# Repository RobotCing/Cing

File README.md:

| [**Úvod**](README.md) |[**Cing**](README-cing-sk.md)  |[**GalejeNextGen**](README-GNG-sk.md)|[**Kontakt**](README-kontakt.md)|[**English version**](README-en.md)|[**Arduino portable**](https://drive.google.com/file/d/1-qsKpOY3mSJC7BOQW4kqXe5UFbl79BuX/view?usp=sharing)|
|:---:|:---:|:---:|:---:|:---:|:---:|
|[Attiny 85](README-Attiny85.md)|[Attiny 84](README-Attiny84.md)|[Atmega 8](README-Atmega8.md)|[Attiny 13](README-Attiny13.md)|[Atmega 328](README-Atmega328.md)|[Atmega 32u4](README-Atmega32u4.md)|

## Úvod:

Každý pozná firmu [Lego](https://www.lego.com/en-us/). Vyrábajú najpopulárnejšie [Lego](https://www.lego.com/en-us/) stavebnice a sety. Vyrábajú <a href="https://www.lego.com/en-us/mindstorms">Lego NXT a Lego EV3</a> sety, ktoré sa jednoducho programujú a konštruujú, ale po naučení sa ich obrázkoveho jednoduchého programovacieho jazyka nemá užívaťeľ ďalšie možnosti ako programovať ich lego stavebnicu. Užívateľovi ostáva jediná možnosť - prejsť na inú platformu, napríklad [Arduino](https://www.arduino.cc/). 

[Arduino](https://www.arduino.cc/) je jedna z najlepších možností, nakoľko je lacnejšie ako akákoľvek iná platforma a taktiež je voľne dostupné. Ak sa užívateľ chce venovať [Arduinu](https://www.arduino.cc/), musí mať znalosti z elektroniky. Avšak tento fakt si mnoho ľudí uvedomí až keď si [Arduino](https://www.arduino.cc/) kúpi a vačšina z nich to vzdá. 

Preto sme vytvroli robota <a href="https://github.com/Galeje/Cing" target= "_blank">Cing</a> - je to multifunkčný a praktický robot pre všetky vekové kategórie od začiatočníkov až po expertov, nakoľko nie je potrebná žiadna znalosť z elektorniky či programovania. Pomocou nami vytvorených <a href="https://github.com/Galeje/Cing/tree/master/libraries" target= "_blank">knižníc</a>, ktoré umožňujü praktické a jednoduché využitie robota <a href="https://github.com/Galeje/Cing" target= "_blank">Cing</a> sa užívateľ naučí rýchlo, hravo a efektívne programovať.

Pre ešte ľahšie programovanie a učenie sa sme vytvorili príručky, ktoré obsahujú všetky programy a následne ich vysvetľujú. Aby užívateľ vedel, ako správne poskladať robota <a href="https://github.com/Galeje/Cing" target= "_blank">Cing</a>, použije opäť nami vytvorený manuál. Po naučení sa základných príkazov si môže vyskúšať cvičenia zo zbierky úloh na plátne s atrakciami.

Po zvládnutí základných aj pokročilých progamovacích príkazov môže používateľ použiť robota <a href="https://github.com/Galeje/Cing" target= "_blank">Cing</a> ako nástroj pre učenie sa elektroniky, nakoľko sa jednoducho dostane k schémam aj príručke, ako ho programovať bez použitia <a href="https://github.com/Galeje/Cing/tree/master/libraries" target= "_blank">knižníc</a>. To znamená, že užívateľ si môže vybrať, ako chce programovať <a href="https://github.com/Galeje/" target= "_blank">Cing-a</a>.

<!---Každú pozná firmu [Lego](https://www.lego.com/en-us/). Vyrábajú najpopulárnejšie [Lego](https://www.lego.com/en-us/) stavebnice a sety. Vyrábajú <a href="https://www.lego.com/en-us/mindstorms">Lego NXT and Lego EV3</a>sety ktoré sa jednoducho programujú a konštruujú, ale po naučení sa ich obrázkoveho jednoduchého programovacieho jazyka nemá užívaťeľ ďalšie možnosti ako programovat ich lego stavebnicu. Užívateľovi ostáva jediná možnosť - Prejisť na inú platformu napríklad [Arduino](https://www.arduino.cc/). [Arduino](https://www.arduino.cc/) je super možnosť nakoľko je Open Source, je lacnejšie, ale užívaťel musí rozumieť elektronike. Tento fakt si mnoho ľudí uvedomí až keď si [Arduino](https://www.arduino.cc/) kúpi a vačšina ľudí to vzdá.
<a href="https://github.com/Galeje/Cing" target= "_blank">Cing</a> rieši tento problém <a href="https://github.com/Galeje/Cing/tree/master/libraries" target= "_blank">knižnicami</a> ktoré umožňujú jednoduché programovanie <a href="https://github.com/Galeje/Cing" target= "_blank">Cing-a</a> v C programovaciom jazyku bez nutnosťi znalosti elektroniky. Taktiež sme vytvorili <a href="https://github.com/Galeje/Cing/blob/master/CINGtlac.pdf">príručky</a>, ktoré naučia užívateľa programovat <a href="https://github.com/Galeje/Cing" target= "_blank">Cing-a</a>.Po naučení sa základných aj pokročilých progamovacích príkazov môže používateľ použiť robota <a href="https://github.com/Galeje/Cing" target= "_blank">Cing</a> ako nástroj pre učenie sa elektroniky, nakoľko sa jednoducho dostane k schémam aj príručke ako ho programovať bez použitia <a href="https://github.com/Galeje/Cing/tree/master/libraries" target= "_blank">knižníc</a>. To znamená, že užívateľ si môže vybrať ako chce programovať <a href="https://github.com/Galeje/Cing" target= "_blank">Cing-a</a>.--->

Projekt používa <a href="https://github.com/MCUdude/MicroCore">MicroCore</a> a <a href="https://github.com/damellis">Damellis</a> <a href="https://github.com/damellis/attiny">ATtiny core</a>.

## Podporte nás:

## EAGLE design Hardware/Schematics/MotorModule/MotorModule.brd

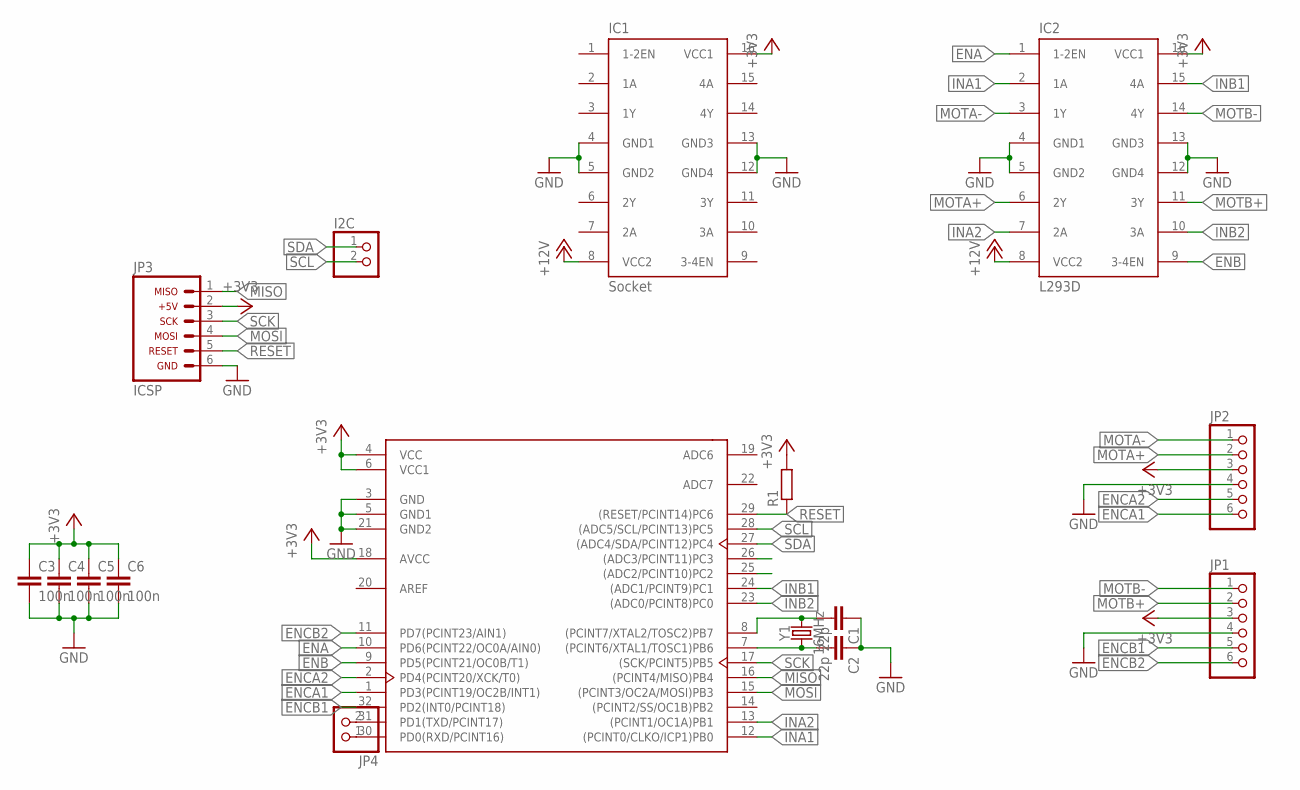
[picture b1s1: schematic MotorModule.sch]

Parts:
C1, C2: 22p; C1206
C3, C4, C5, C6: 100n; C1206
I2C: PINHD-1X2; 1X02
IC1: Socket; L293
IC2: L293D; L293
JP1, JP2: PINHD-1X6/90; 1X06/90
JP3: ICSP_HEADER
JP4: PINHD-1X2; 1X02
R1: R-EU_M1206; M1206
U1: ATMEGA328P-AU; TQFP-32
Y1: 16MHz; CRYSTAL-SMD-5X3.2-4PAD

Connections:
+3V3: C3.1, C4.1, C5.1, C6.1, IC1.16 (VCC1), IC2.16 (VCC1), JP1.3, JP2.3, JP3.2, R1.2, U1.4 (VCC), U1.6 (VCC1), U1.18 (AVCC)
+12V: IC1.8 (VCC2), IC2.8 (VCC2)
AREF: U1.20 (AREF)
ENA: IC2.1 (1-2EN), U1.10 (PD6(PCINT22/OC0A/AIN0))
ENB: IC2.9 (3-4EN), U1.9 (PD5(PCINT21/OC0B/T1))
ENCA1: JP2.6, U1.1 (PD3(PCINT19/OC2B/INT1))
ENCA2: JP2.5, U1.2 (PD4(PCINT20/XCK/T0))
ENCB1: JP1.5, U1.32 (PD2(INT0/PCINT18))
ENCB2: JP1.6, U1.11 (PD7(PCINT23/AIN1))
GND: C1.1, C2.1, C3.2, C4.2, C5.2, C6.2, IC1.4 (GND1), IC1.5 (GND2), IC1.12 (GND4), IC1.13 (GND3), IC2.4 (GND1), IC2.5 (GND2), IC2.12 (GND4), IC2.13 (GND3), JP1.4, JP2.4, JP3.6, U1.3 (GND), U1.5 (GND1), U1.21 (GND2)
INA1: IC2.2 (1A), U1.12 ((PCINT0/CLKO/ICP1)PB0)
INA2: IC2.7 (2A), U1.13 ((PCINT1/OC1A)PB1)
INB1: IC2.15 (4A), U1.24 ((ADC1/PCINT9)PC1)
INB2: IC2.10 (3A), U1.23 ((ADC0/PCINT8)PC0)
MISO: JP3.1, U1.16 ((PCINT4/MISO)PB4)
MOSI: JP3.4, U1.15 ((PCINT3/OC2A/MOSI)PB3)
MOTA+: IC2.6 (2Y), JP2.2
MOTA-: IC2.3 (1Y), JP2.1
MOTB+: IC2.11 (3Y), JP1.2
MOTB-: IC2.14 (4Y), JP1.1
unnamed: C1.2, U1.8 ((PCINT7/XTAL2/TOSC2)PB7), Y1.3 (2)
unnamed: C2.2, U1.7 ((PCINT6/XTAL1/TOSC1)PB6), Y1.1
unnamed: JP4.1, U1.30 (PD0(RXD/PCINT16))
unnamed: JP4.2, U1.31 (PD1(TXD/PCINT17))
RESET: JP3.5, R1.1, U1.29 ((RESET/PCINT14)PC6)
SCK: JP3.3, U1.17 ((SCK/PCINT5)PB5)
SCL: I2C.2, U1.28 ((ADC5/SCL/PCINT13)PC5)
SDA: I2C.1, U1.27 ((ADC4/SDA/PCINT12)PC4)

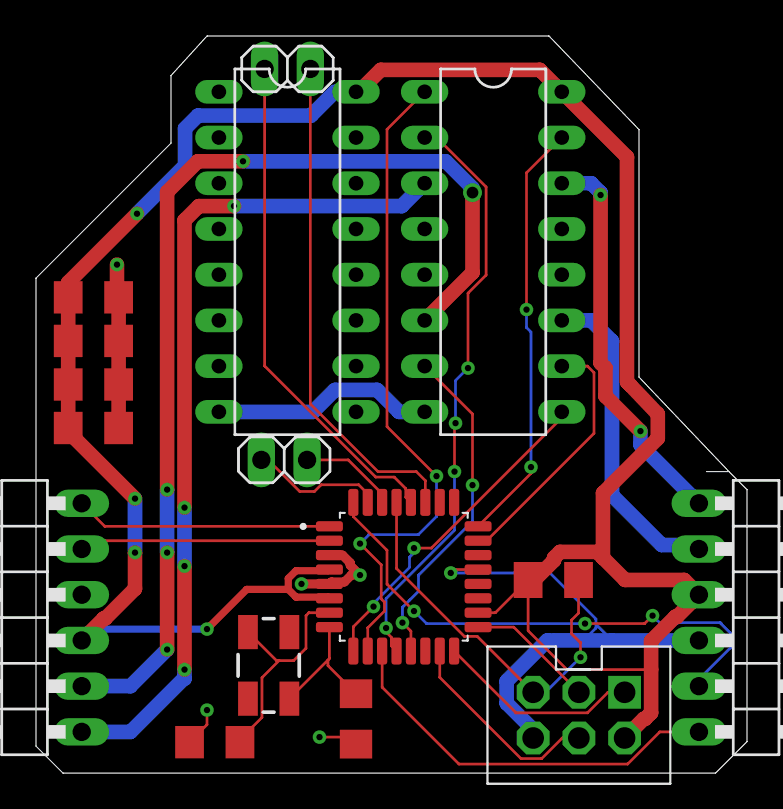
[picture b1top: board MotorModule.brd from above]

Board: 2 copper layers, 39.5 x 41.0 mm, 16 parts (0 on the bottom side), 27 nets.

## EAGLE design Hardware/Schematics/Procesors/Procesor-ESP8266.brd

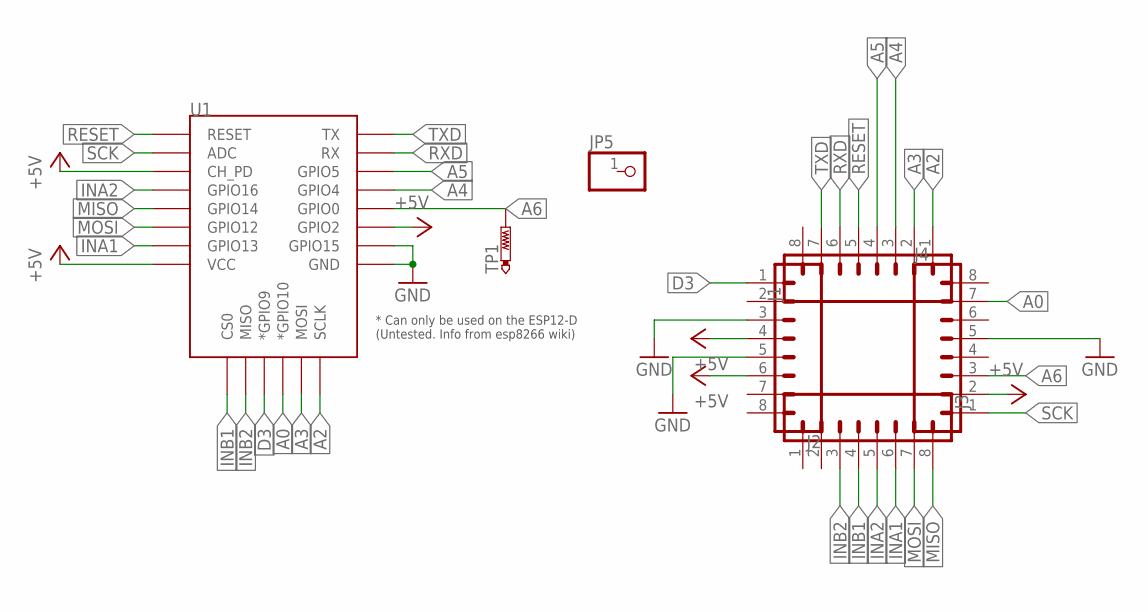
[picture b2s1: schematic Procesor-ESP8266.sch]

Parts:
J1, J2, J3, J4: CONN_08SMD-STRAIGHT-ALT-FEMALE; 1X08_SMD_ALT
JP5: PINHD-1X1; 1X01
TP1: PTR1B1,27; B1,27
U1: ESP12ESMD; ESP12E-SMD

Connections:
+5V: J2.4, J2.6, J4.2, U1.CH_PD, U1.GPIO2, U1.VCC
A0: J4.7, U1.GPIO10 (*GPIO10)
A2: J1.1, U1.SCLK
A3: J1.2, U1.MOSI
A4: J1.3, U1.GPIO4
A5: J1.4, U1.GPIO5
A6: J4.3, TP1.TP, U1.GPIO0
D3: J2.1, U1.GPIO9 (*GPIO9)
GND: J2.3, J2.5, J4.5, U1.GND, U1.GPIO15
INA1: J3.6, U1.GPIO13
INA2: J3.5, U1.GPIO16
INB1: J3.4, U1.CS0
INB2: J3.3, U1.MISO
MISO: J3.8, U1.GPIO14
MOSI: J3.7, U1.GPIO12
RESET: J1.5, U1.RESET
RXD: J1.6, U1.RXD0 (RX)
SCK: J4.1, U1.ADC
TXD: J1.7, U1.TXD0 (TX)

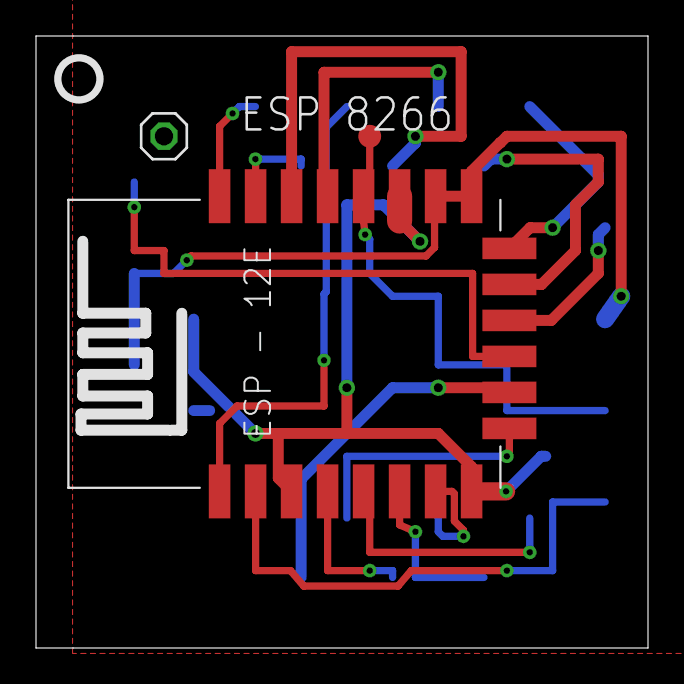
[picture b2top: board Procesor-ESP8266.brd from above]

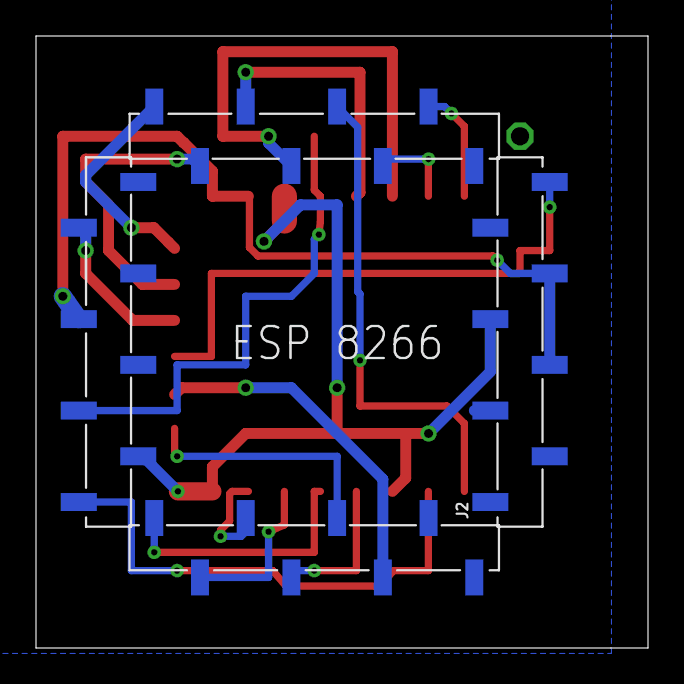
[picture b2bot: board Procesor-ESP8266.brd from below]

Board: 2 copper layers, 34.0 x 34.0 mm, 7 parts (4 on the bottom side), 19 nets.

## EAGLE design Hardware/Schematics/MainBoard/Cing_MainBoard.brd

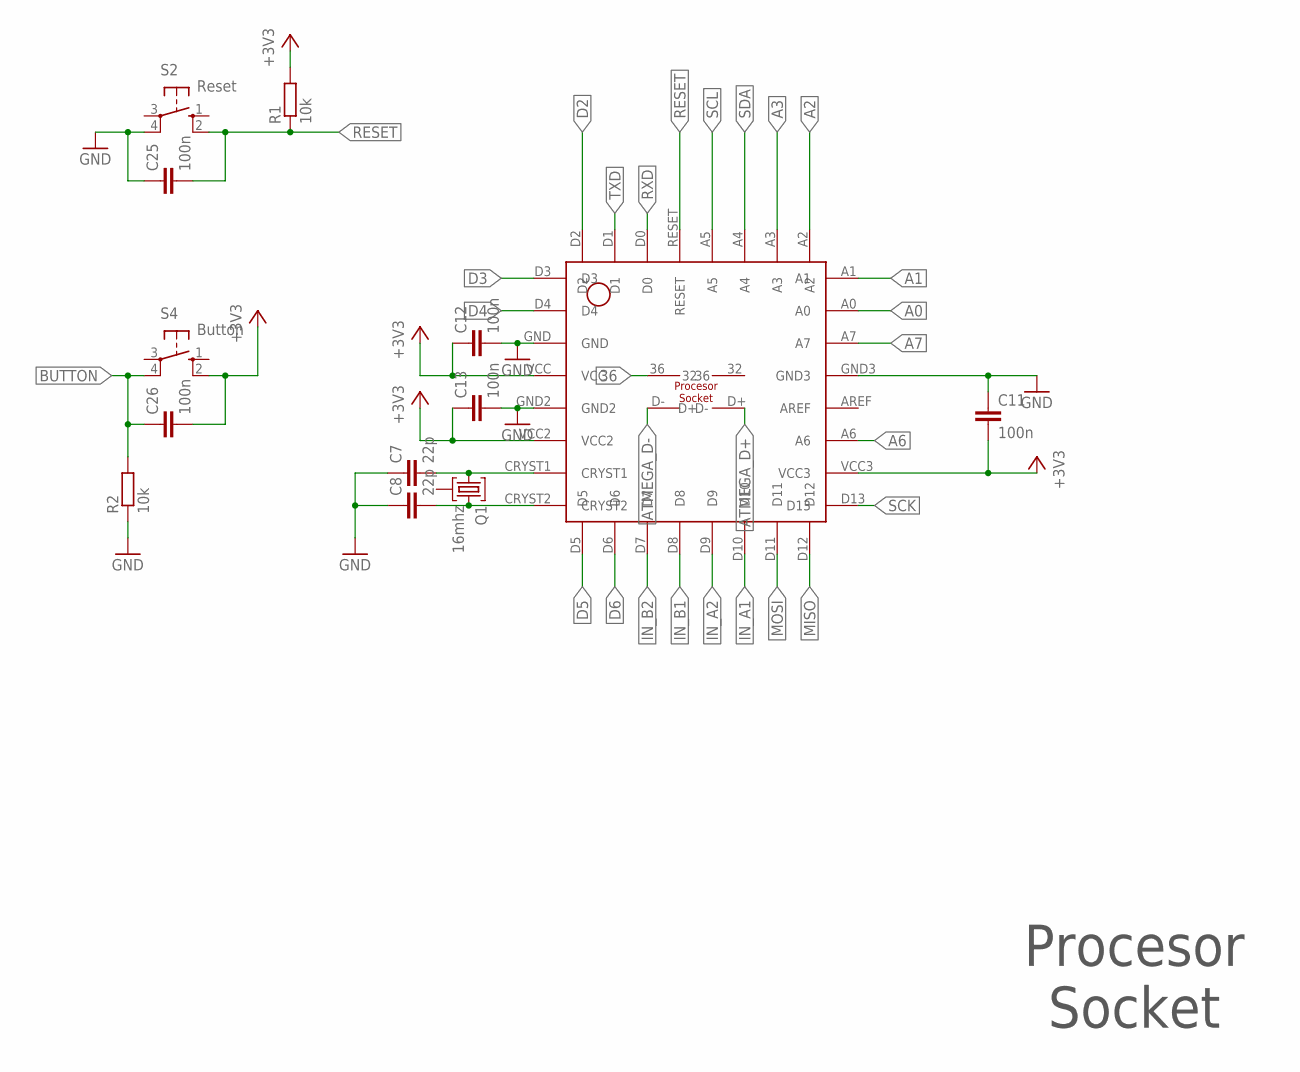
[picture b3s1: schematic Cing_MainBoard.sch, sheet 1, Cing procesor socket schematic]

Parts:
C7, C8: 22p; C1206
C11, C12, C13, C25, C26: 100n; C1206
Q1: 16mhz; HC49U
R1, R2: 10k; R1206
S2: Reset; B3F-10XX
S4: Button; B3F-10XX
U$1: PROCESSOR-SOCKET_PCB

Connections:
36: U$1.36; also elsewhere on the board
+3V3: C11.2, C12.1, C13.1, C26.2, R1.2, S4.2 (S1), U$1.VCC, U$1.VCC2, U$1.VCC3; also elsewhere on the board
A0: U$1.A0; also elsewhere on the board
A1: U$1.A1; also elsewhere on the board
A2: U$1.A2; also elsewhere on the board
A3: U$1.A3; also elsewhere on the board
A6: U$1.A6; also elsewhere on the board
A7: U$1.A7; also elsewhere on the board
ATMEGA_D+: U$1.D+; also elsewhere on the board
ATMEGA_D-: U$1.D-; also elsewhere on the board
BUTTON: C26.1, R2.2, S4.4 (P1); also elsewhere on the board
D2: U$1.D2; also elsewhere on the board
D3: U$1.D3; also elsewhere on the board
D4: U$1.D4; also elsewhere on the board
D5: U$1.D5; also elsewhere on the board
D6: U$1.D6; also elsewhere on the board
GND: C7.1, C8.1, C11.1, C12.2, C13.2, C25.1, R2.1, S2.4 (P1), U$1.GND, U$1.GND2, U$1.GND3; also elsewhere on the board
IN_A1: U$1.D10; also elsewhere on the board
IN_A2: U$1.D9; also elsewhere on the board
IN_B1: U$1.D8; also elsewhere on the board
IN_B2: U$1.D7; also elsewhere on the board
MISO: U$1.D12; also elsewhere on the board
MOSI: U$1.D11; also elsewhere on the board
unnamed: C8.2, Q1.3, U$1.CRYST2
unnamed: C7.2, Q1.1, U$1.CRYST1
RESET: C25.2, R1.1, S2.2 (S1), U$1.RESET; also elsewhere on the board
RXD: U$1.D0; also elsewhere on the board
SCK: U$1.D13; also elsewhere on the board
SCL: U$1.A5; also elsewhere on the board
SDA: U$1.A4; also elsewhere on the board
TXD: U$1.D1; also elsewhere on the board

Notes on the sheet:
Procesor Socket

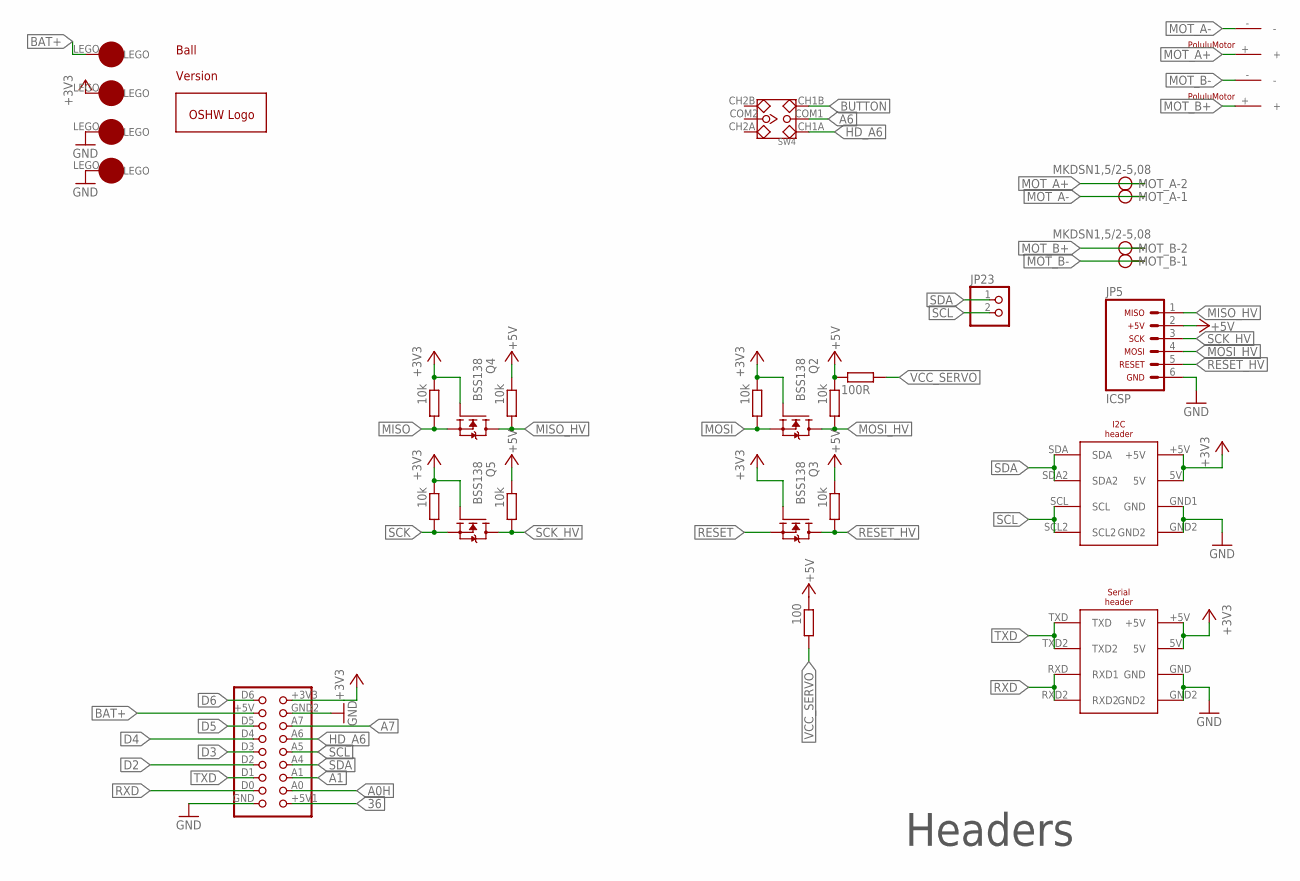
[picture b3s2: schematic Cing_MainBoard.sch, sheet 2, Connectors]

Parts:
JP5: ICSP; ICSP_HEADER
JP23: PINHD-1X2; 1X02
MOT_A: MKDSN1,5/2-5,08
MOT_B: MKDSN1,5/2-5,08
Q2, Q3, Q4, Q5: BSS138; SOT23
R33, R34, R35, R37, R38, R39, R40: 10k; R1206
R36: 100; R1206
R44: 100R; R1206
SW4: USB_SWITCH
U$2: Header 2; BIG_HEADER
U$3: I2C_HEADER; I2_HEADER
U$4: SERIAL_HEADER
U$9, U$24: POLULU_MOTOR
U$16: BAT+; LEGO-1X1
U$17: 3.3V; LEGO-1X1
U$18, U$19: GND; LEGO-1X1
U$20: BALL
U$22: OPENSOURCE; OSHW_5MM
VERSION: 4.1; VERSION

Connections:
36: U$2.+5V1; also elsewhere on the board
+3V3: Q2.1 (G), Q3.1 (G), Q4.1 (G), Q5.1 (G), R34.1, R38.1, R40.1, U$2.+3V3, U$3.5V, U$3.+5V, U$4.5V, U$4.+5V, U$17.LEGO; also elsewhere on the board
+5V: JP5.2, R33.1, R35.1, R36.1, R37.1, R39.1, R44.1
A0H: U$2.A0; also elsewhere on the board
A1: U$2.A1; also elsewhere on the board
A6: SW4.COM1; also elsewhere on the board
A7: U$2.A7; also elsewhere on the board
BAT+: U$2.+5V, U$16.LEGO; also elsewhere on the board
BUTTON: SW4.CH1B; also elsewhere on the board
D2: U$2.D2; also elsewhere on the board
D3: U$2.D3; also elsewhere on the board
D4: U$2.D4; also elsewhere on the board
D5: U$2.D5; also elsewhere on the board
D6: U$2.D6; also elsewhere on the board
GND: JP5.6, U$2.GND, U$2.GND2 (GND1), U$3.GND1 (GND), U$3.GND2, U$4.GND, U$4.GND2, U$18.LEGO, U$19.LEGO; also elsewhere on the board
HD_A6: SW4.CH1A, U$2.A6
MISO: Q4.2 (S), R38.2; also elsewhere on the board
MISO_HV: JP5.1, Q4.3 (D), R37.2
MOSI: Q2.2 (S), R34.2; also elsewhere on the board
MOSI_HV: JP5.4, Q2.3 (D), R33.2
MOT_A+: MOT_A.2, U$24.+; also elsewhere on the board
MOT_A-: MOT_A.1, U$24.-; also elsewhere on the board
MOT_B+: MOT_B.2, U$9.+; also elsewhere on the board
MOT_B-: MOT_B.1, U$9.-; also elsewhere on the board
RESET: Q3.2 (S); also elsewhere on the board
RESET_HV: JP5.5, Q3.3 (D), R35.2
RXD: U$2.D0, U$4.RXD (RXD1), U$4.RXD2; also elsewhere on the board
SCK: Q5.2 (S), R40.2; also elsewhere on the board
SCK_HV: JP5.3, Q5.3 (D), R39.2
SCL: JP23.2, U$2.A5, U$3.SCL, U$3.SCL2; also elsewhere on the board
SDA: JP23.1, U$2.A4, U$3.SDA, U$3.SDA2; also elsewhere on the board
TXD: U$2.D1, U$4.TXD, U$4.TXD2; also elsewhere on the board
VCC_SERVO: R36.2, R44.2; also elsewhere on the board

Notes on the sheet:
Headers

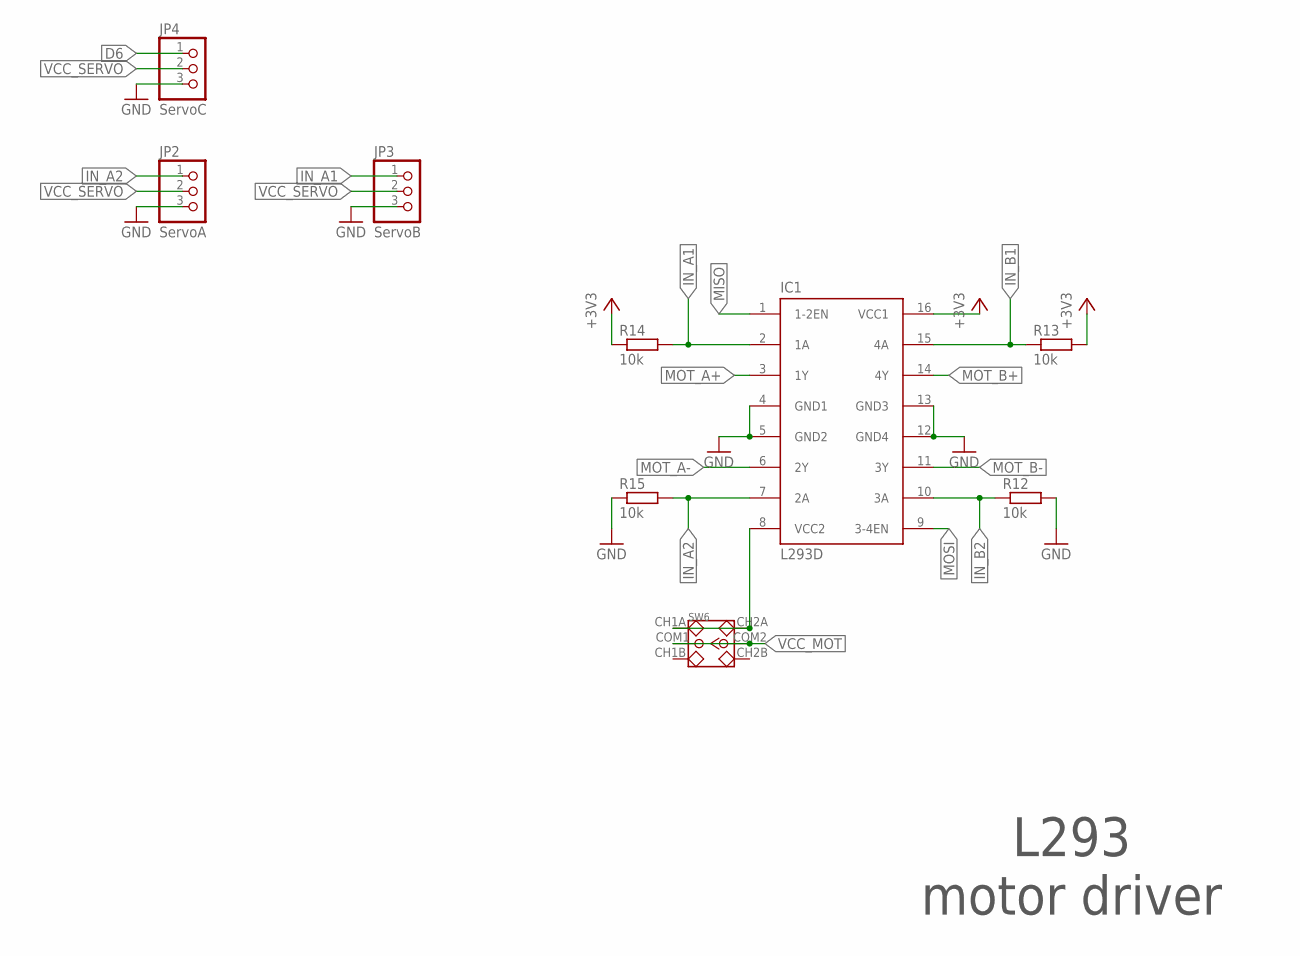
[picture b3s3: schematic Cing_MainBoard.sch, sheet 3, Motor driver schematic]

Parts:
IC1: L293D; L293
JP2: ServoA; 1X03
JP3: ServoB; 1X03
JP4: ServoC; 1X03
R12, R13, R14, R15: 10k; R1206
SW6: USB_SWITCH

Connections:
+3V3: IC1.16 (VCC1), R13.2, R14.1; also elsewhere on the board
D6: JP4.1; also elsewhere on the board
GND: IC1.4 (GND1), IC1.5 (GND2), IC1.12 (GND4), IC1.13 (GND3), JP2.3, JP3.3, JP4.3, R12.2, R15.1; also elsewhere on the board
IN_A1: IC1.2 (1A), JP3.1, R14.2; also elsewhere on the board
IN_A2: IC1.7 (2A), JP2.1, R15.2; also elsewhere on the board
IN_B1: IC1.15 (4A), R13.1; also elsewhere on the board
IN_B2: IC1.10 (3A), R12.1; also elsewhere on the board
MISO: IC1.1 (1-2EN); also elsewhere on the board
MOSI: IC1.9 (3-4EN); also elsewhere on the board
MOT_A+: IC1.3 (1Y); also elsewhere on the board
MOT_A-: IC1.6 (2Y); also elsewhere on the board
MOT_B+: IC1.14 (4Y); also elsewhere on the board
MOT_B-: IC1.11 (3Y); also elsewhere on the board
unnamed: IC1.8 (VCC2), SW6.CH1A, SW6.CH2A
VCC_MOT: SW6.COM1, SW6.COM2; also elsewhere on the board
VCC_SERVO: JP2.2, JP3.2, JP4.2; also elsewhere on the board

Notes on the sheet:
L293 motor driver

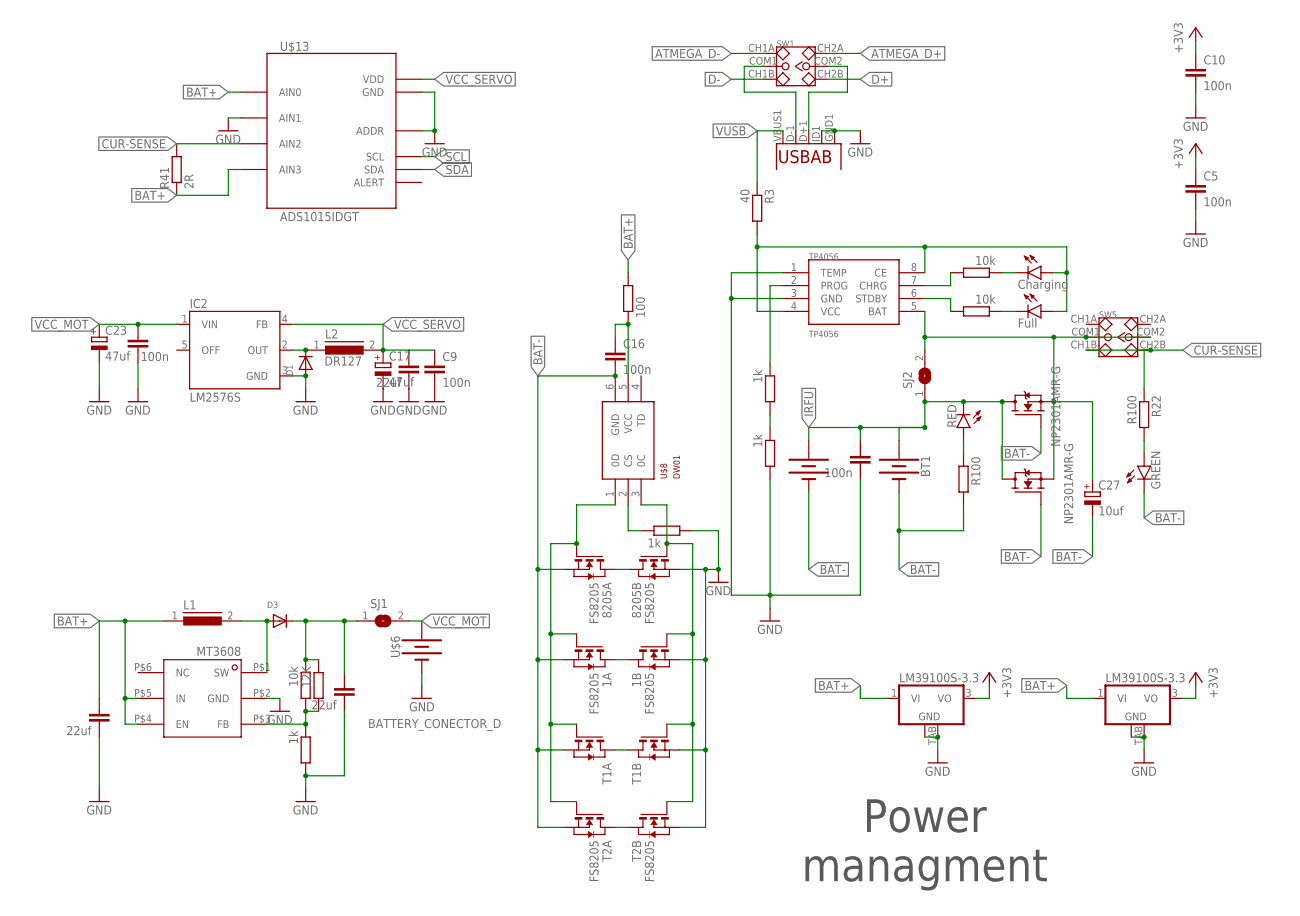
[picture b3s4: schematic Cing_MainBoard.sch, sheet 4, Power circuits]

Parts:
1, 8205: FS8205; TSSOP-8
BT1: BATTERY-AA_KIT; BATTERY-AA-KIT
C1, C5, C9, C10, C16, C24: 100n; C1206
C4, C14, C15: 22uf; C1206
C17, C23: 47uf; 153CLV-0505
C27: 10uf; 153CLV-0505
D1, D3: DIODESMA; SMADIODE
IC2: LM2576S; TO263-5
L1: DR125
L2: DR127
LED1: Charging; 1206
ON: GREEN; 1206
Q6, Q7: NP2301AMR-G; SOT23
R3: 40; R1206
R4, R8, R46, R47: 1k; R1206
R5, R9, R11: 10k; R1206
R6, R22: R100; R1206
R41: 2R; R1206
R48: 100; R1206
R49: 12K; R1206
REV: RED; 1206
SJ1: SJW
SJ2: SJ
SW1, SW5: USB_SWITCH
T1, T2: FS8205; TSSOP-8
TP4056: TP4056
U1: MICRO_USB""; USB-MICRO-SMD
U$5: MT3608SOT23-6; SOT23-6
U$6, U$7: BATTERY_CONECTOR_D
U$8: DW01; SOT23-6
U$13: ADS1015IDGT; MSOP10_0.5
U$25, U$26: LM39100S-3.3
YELLOW: Full; 1206

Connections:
+3V3: C5.1, C10.1, U$25.3 (VO), U$26.3 (VO); also elsewhere on the board
ATMEGA_D+: SW1.CH2A; also elsewhere on the board
ATMEGA_D-: SW1.CH1A; also elsewhere on the board
BAT+: C15.1, L1.1, R41.1, R48.2, U$5.P$4 (EN), U$5.P$5 (IN), U$13.4 (AIN0), U$13.7 (AIN3), U$25.1 (VI), U$26.1 (VI); also elsewhere on the board
BAT-: 1.2 (S), 1.3 (S), 8205.2 (S), 8205.3 (S), BT1.GND@1 (-), C16.2, C27.-, ON.C, Q6.1 (G), Q7.1 (G), R6.1, T1.2 (S), T1.3 (S), T2.2 (S), T2.3 (S), U$7.-, U$8.6 (GND)
CUR-SENSE: R22.1, R41.2, SW5.CH1B, SW5.CH2B, U$13.6 (AIN2)
D+: SW1.CH2B; also elsewhere on the board
D-: SW1.CH1B; also elsewhere on the board
GND: 1.6 (S), 1.7 (S), 8205.6 (S), 8205.7 (S), C1.2, C4.2, C5.2, C9.2, C10.2, C14.2, C15.2, C17.-, C23.-, C24.2, D1.A, IC2.3 (GND), R8.2, R46.2, R47.2, T1.6 (S), T1.7 (S), T2.6 (S), T2.7 (S), TP4056.1 (TEMP), TP4056.3 (GND), U1.GND1 (GND), U1.ID1 (USBID), U$5.P$2 (GND), U$6.-, U$13.1 (ADDR), U$13.3 (GND), U$13.5 (AIN1), U$25.2 (GND), U$25.TAB (GND_2), U$26.2 (GND), U$26.TAB (GND_2); also elsewhere on the board
IRFU: BT1.PWR@1 (+), C1.1, Q6.3 (D), Q7.3 (D), REV.C, SJ2.1, U$7.+
unnamed: 1.1 (D), 1.8 (D)
unnamed: R6.2, REV.A
unnamed: R4.2, R8.1
unnamed: SW1.COM1, U1.D-1 (D-)
unnamed: LED1.C, R5.1
unnamed: SW1.COM2, U1.D+1 (D+)
unnamed: R11.1, YELLOW.C
unnamed: R11.2, TP4056.6 (STDBY)
unnamed: R5.2, TP4056.7 (CHRG)
unnamed: D1.C, IC2.2 (OUT), L2.1
unnamed: LED1.A, R3.2, TP4056.4 (VCC), TP4056.8 (CE), YELLOW.A
unnamed: C27.+, Q6.2 (S), Q7.2 (S), SJ2.2, SW5.COM1, SW5.COM2, TP4056.5 (BAT)
unnamed: R4.1, TP4056.2 (PROG)
unnamed: ON.A, R22.2
unnamed: R9.2, R46.1, R49.2, U$5.P$3 (FB)
unnamed: D3.A, L1.2, U$5.P$1 (SW)
unnamed: C14.1, D3.C, R9.1, R49.1, SJ1.1
unnamed: 8205.1 (D), 8205.8 (D)
unnamed: 1.4 (G), 8205.4 (G), T1.4 (G), T2.4 (G), U$8.1 (0D)
unnamed: 1.5 (G), 8205.5 (G), T1.5 (G), T2.5 (G), U$8.3 (0C)
unnamed: C16.1, R48.1, U$8.5 (VCC)
unnamed: R47.1, U$8.2 (CS)
unnamed: T1.1 (D), T1.8 (D)
unnamed: T2.1 (D), T2.8 (D)
SCL: U$13.10 (SCL); also elsewhere on the board
SDA: U$13.9 (SDA); also elsewhere on the board
VCC_MOT: C23.+, C24.1, IC2.1 (VIN), SJ1.2, U$6.+; also elsewhere on the board
VCC_SERVO: C4.1, C9.1, C17.+, IC2.4 (FB), L2.2, U$13.8 (VDD); also elsewhere on the board
VUSB: R3.1, U1.VBUS1 (VBUS); also elsewhere on the board

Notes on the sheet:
Power managment

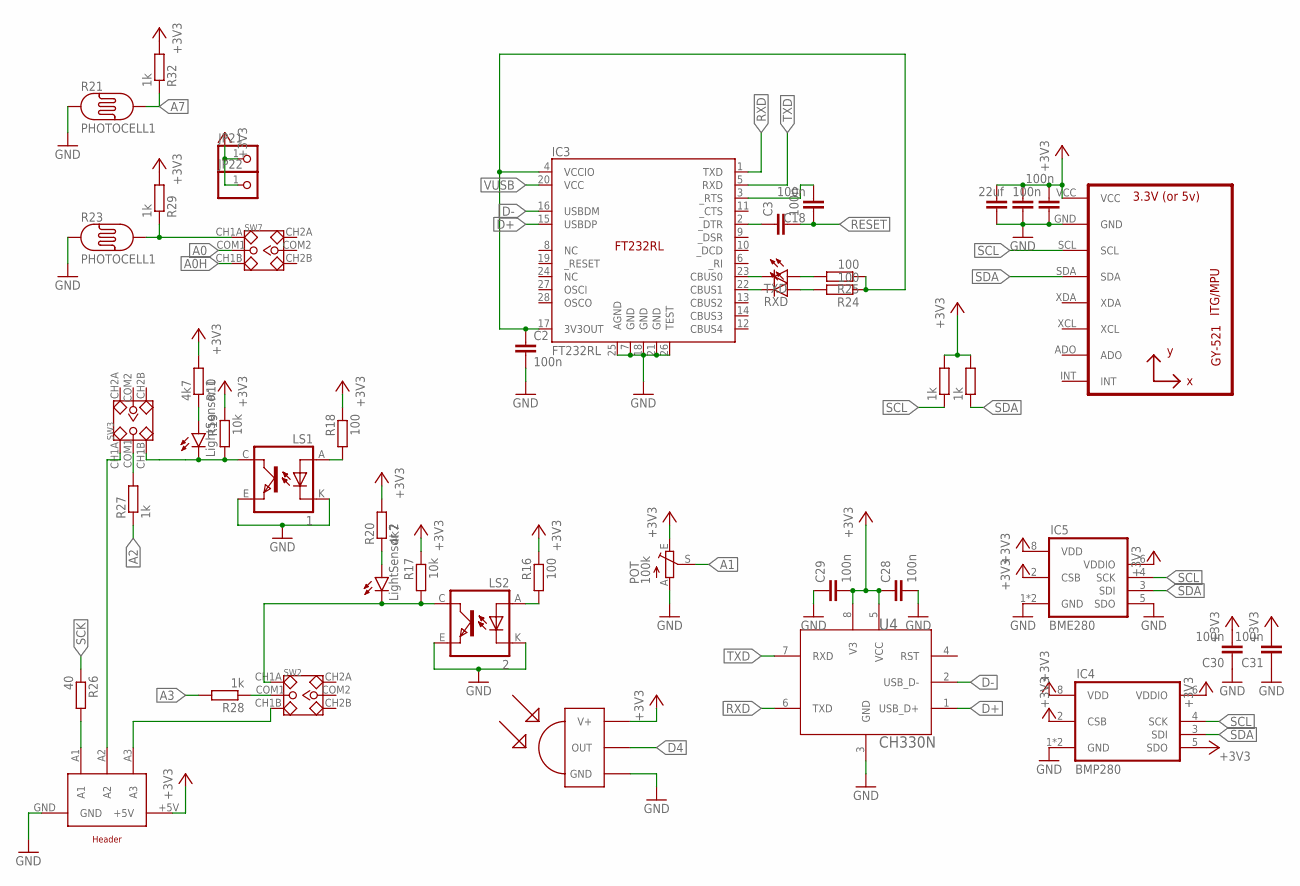
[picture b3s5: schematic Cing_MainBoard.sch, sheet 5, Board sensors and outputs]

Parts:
C2, C3, C6, C18, C21, C28, C29, C30, C31: 100n; C1206
C22: 22uf; C1206
IC3: FT232RL
IC4: BMP280
IC5: BME280
JP21, JP22: PINHD-1X1; 1X01
LED3: RXD; 1206
LS1: 1; TCRT5000
LS2: 2; TCRT5000
POT: 100k; RJ9W
R10, R20: 4k7; R1206
R16, R18, R24, R25: 100; R1206
R17, R19: 10k; R1206
R21, R23: PHOTOCELL1; LDR_OFFBOARD
R26: 40; R1206
R27, R28, R29, R30, R31, R32: 1k; R1206
SW2, SW3, SW7: USB_SWITCH
TSOP4838: TSOP4838; TSOP18XX
TXD: TXD; 1206
TXD1: LightSensor 1; 1206
TXD2: LightSensor 2; 1206
U3: MPU-6050MPU6050; MPU-6050
U4: CH330N; SOIC-8N
U$12: CONNECTOR_1X5

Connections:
+3V3: C6.2, C21.2, C22.1, C28.1, C29.2, C30.2, C31.2, IC4.2 (CSB), IC4.5 (SDO), IC4.6 (VDDIO), IC4.8 (VDD), IC5.2 (CSB), IC5.6 (VDDIO), IC5.8 (VDD), JP21.1, JP22.1, POT.E, R10.2, R16.1, R17.1, R18.1, R19.1, R20.2, R29.2, R30.2, R31.2, R32.2, TSOP4838.VCC (V+), U3.VCC, U4.5 (VCC), U4.8 (V3), U$12.+5V; also elsewhere on the board
A0: SW7.COM1; also elsewhere on the board
A0H: SW7.CH1B; also elsewhere on the board
A1: POT.S; also elsewhere on the board
A2: R27.1; also elsewhere on the board
A3: R28.2; also elsewhere on the board
A7: R21.2, R32.1; also elsewhere on the board
D4: TSOP4838.OUT; also elsewhere on the board
D+: IC3.15 (USBDP), U4.1 (USB_D+); also elsewhere on the board
D-: IC3.16 (USBDM), U4.2 (USB_D-); also elsewhere on the board
GND: C2.2, C6.1, C21.1, C22.2, C28.2, C29.1, C30.1, C31.1, IC3.7 (GND), IC3.18 (GND), IC3.21 (GND), IC3.25 (AGND), IC3.26 (TEST), IC4.1 (GND), IC4.7 (GND), IC5.1 (GND), IC5.5 (SDO), IC5.7 (GND), LS1.E (EMITTER), LS1.K (CATHODE), LS2.E (EMITTER), LS2.K (CATHODE), POT.A, R21.1, R23.1, TSOP4838.GND, U3.GND, U4.3 (GND), U$12.GND; also elsewhere on the board
unnamed: R28.1, SW2.COM1
unnamed: R10.1, TXD1.A
unnamed: R20.1, TXD2.A
unnamed: LS2.A (ANODE), R16.2
unnamed: LS1.A (ANODE), R18.2
unnamed: LS1.C (COLLECTOR), R19.2, SW3.CH1B, TXD1.C
unnamed: SW3.CH1A, U$12.A2
unnamed: LED3.A, R24.2
unnamed: IC3.22 (CBUS1), LED3.C
unnamed: R25.2, TXD.A
unnamed: C3.1, IC3.2 (_DTR)
unnamed: C2.1, IC3.4 (VCCIO), IC3.17 (3V3OUT), R24.1, R25.1
unnamed: SW2.CH1B, U$12.A3
unnamed: R26.2, U$12.A1
unnamed: R27.2, SW3.COM1
unnamed: LS2.C (COLLECTOR), R17.2, SW2.CH1A, TXD2.C
unnamed: C18.2, IC3.3 (_RTS)
unnamed: R23.2, R29.1, SW7.CH1A
RESET: C3.2, C18.1; also elsewhere on the board
RXD: IC3.1 (TXD), U4.6 (TXD); also elsewhere on the board
SCK: R26.1; also elsewhere on the board
SCL: IC4.4 (SCK), IC5.4 (SCK), R30.1, U3.SCL; also elsewhere on the board
SDA: IC4.3 (SDI), IC5.3 (SDI), R31.1, U3.SDA; also elsewhere on the board
T: IC3.23 (CBUS0), TXD.C
TXD: IC3.5 (RXD), U4.7 (RXD); also elsewhere on the board
VUSB: IC3.20 (VCC); also elsewhere on the board

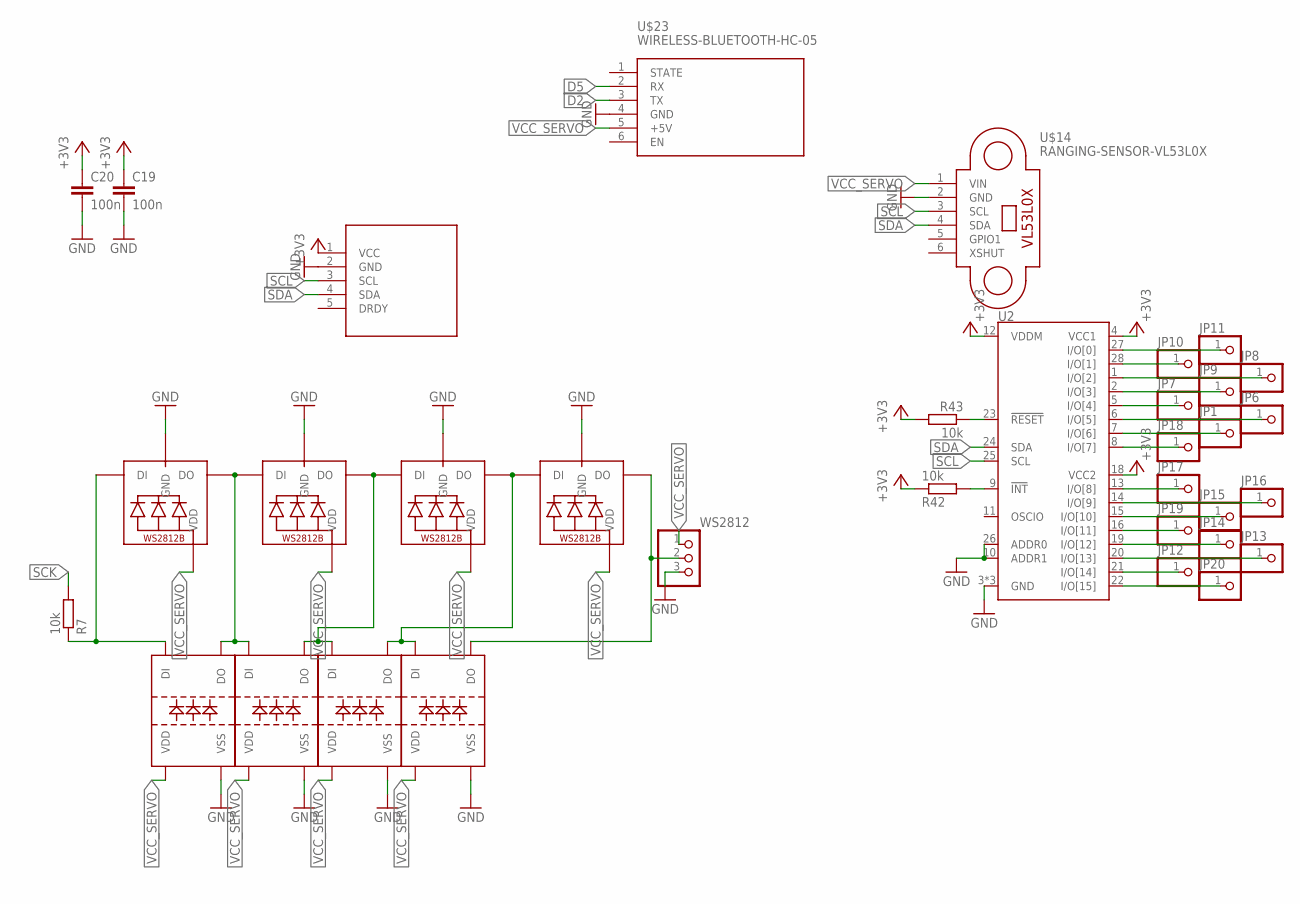
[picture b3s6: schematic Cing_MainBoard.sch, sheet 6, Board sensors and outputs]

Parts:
C19, C20: 100n; C1206
JP1, JP6, JP7, JP8, JP9, JP10, JP11, JP12, JP13, JP14, JP15, JP16, JP17, JP18, JP19, JP20: PINHD-1X1; 1X01
LED4, LED9, LED10, LED11: WS2812B3535; LED3535
LED5, LED6, LED7, LED8: WS2812B
R7, R42, R43: 10k; R1206
U2: SX1509; QFN-28
U$14: RANGING-SENSOR-VL53L0X
U$15: COMPASS-HMC5883L
U$23: WIRELESS-BLUETOOTH-HC-05
WS2812: PINHD-1X3; 1X03

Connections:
+3V3: C19.1, C20.1, R42.1, R43.2, U2.4 (VCC1), U2.12 (VDDM), U2.18 (VCC2), U$15.1 (VCC); also elsewhere on the board
D2: U$23.3 (TX); also elsewhere on the board
D5: U$23.2 (RX); also elsewhere on the board
GND: C19.2, C20.2, LED4.4 (GND), LED5.3 (VSS), LED6.3 (VSS), LED7.3 (VSS), LED8.3 (VSS), LED9.4 (GND), LED10.4 (GND), LED11.4 (GND), U2.3 (GND), U2.10 (ADDR1), U2.17 (GND), U2.26 (ADDR0), U2.29 (GND), U$14.2 (GND), U$15.2 (GND), U$23.4 (GND), WS2812.3; also elsewhere on the board
unnamed: LED5.2 (DO), LED6.4 (DI), LED9.1 (DI), LED10.3 (DO)
unnamed: LED4.1 (DI), LED6.2 (DO), LED7.4 (DI), LED9.3 (DO)
unnamed: LED4.3 (DO), LED7.2 (DO), LED8.4 (DI), LED11.1 (DI)
unnamed: LED5.4 (DI), LED10.1 (DI), R7.1
unnamed: R42.2, U2.9 (!INT)
unnamed: R43.1, U2.23 (!RESET)
unnamed: JP1.1, U2.7 (I/O[6])
unnamed: JP6.1, U2.6 (I/O[5])
unnamed: JP7.1, U2.5 (I/O[4])
unnamed: LED8.2 (DO), LED11.3 (DO), WS2812.2
unnamed: JP8.1, U2.1 (I/O[2])
unnamed: JP9.1, U2.2 (I/O[3])
unnamed: JP10.1, U2.28 (I/O[1])
unnamed: JP11.1, U2.27 (I/O[0])
unnamed: JP12.1, U2.21 (I/O[14])
unnamed: JP13.1, U2.20 (I/O[13])
unnamed: JP14.1, U2.19 (I/O[12])
unnamed: JP15.1, U2.15 (I/O[10])
unnamed: JP16.1, U2.14 (I/O[9])
unnamed: JP17.1, U2.13 (I/O[8])
unnamed: JP18.1, U2.8 (I/O[7])
unnamed: JP19.1, U2.16 (I/O[11])
unnamed: JP20.1, U2.22 (I/O[15])
SCK: R7.2; also elsewhere on the board
SCL: U2.25 (SCL), U$14.3 (SCL), U$15.3 (SCL); also elsewhere on the board
SDA: U2.24 (SDA), U$14.4 (SDA), U$15.4 (SDA); also elsewhere on the board
VCC_SERVO: LED4.2 (VDD), LED5.1 (VDD), LED6.1 (VDD), LED7.1 (VDD), LED8.1 (VDD), LED9.2 (VDD), LED10.2 (VDD), LED11.2 (VDD), U$14.1 (VIN), U$23.5 (+5V), WS2812.1; also elsewhere on the board

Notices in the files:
parts and their libraries:
diy-modules: Released under the Creative Commons Attribution 4.0 International License: http://creativecommons.org/licenses/by/4.0
SparkFun-Clocks: Licensing: Creative Commons ShareAlike 4.0 International - https://creativecommons.org/licenses/by-sa/4.0
